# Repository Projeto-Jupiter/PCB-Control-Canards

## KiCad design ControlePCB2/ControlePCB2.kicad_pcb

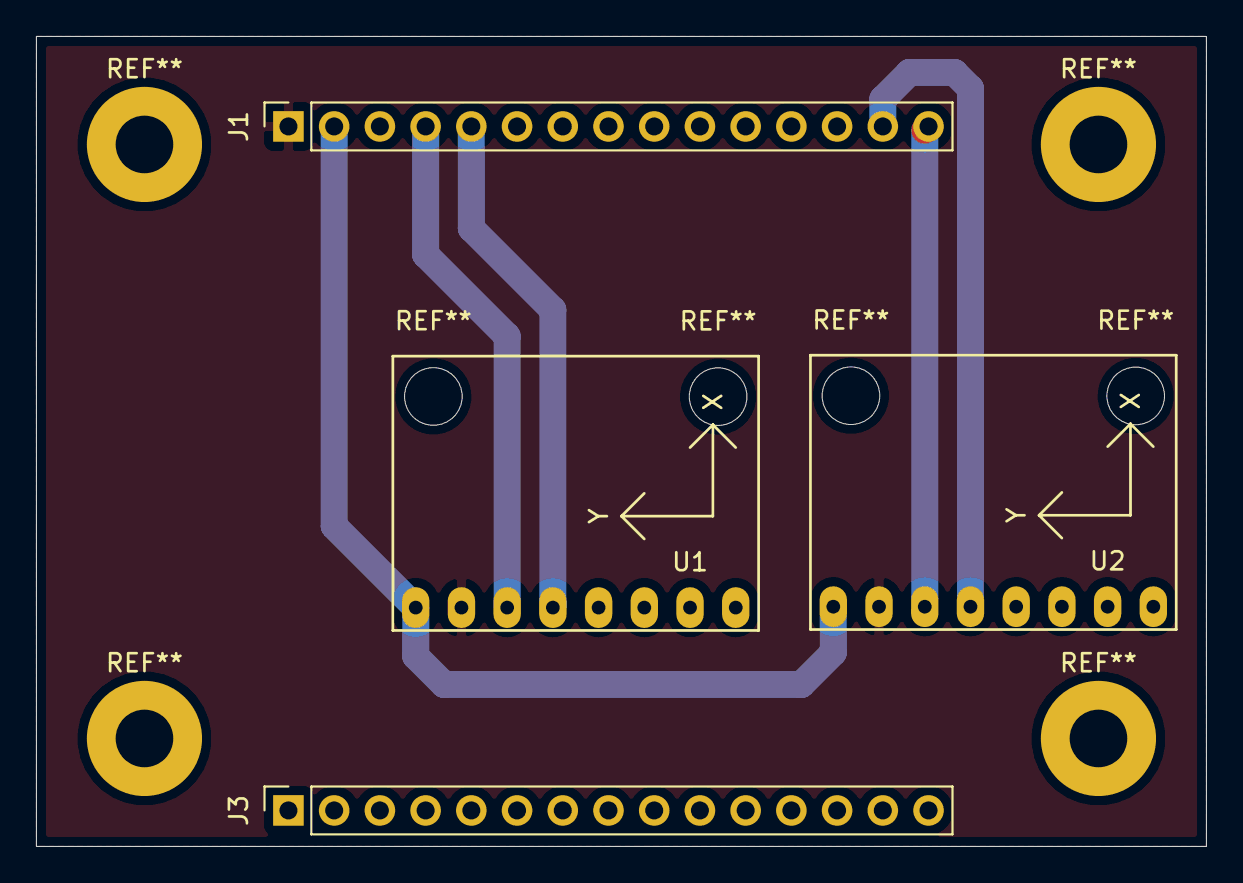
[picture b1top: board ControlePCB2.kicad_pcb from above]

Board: 2 copper layers, 65.0 x 45.0 mm, 4 parts (0 on the bottom side), 6 nets.

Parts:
J1, J3: Conn_01x15_Female; PinSocket_1x15_P2.54mm_Vertical
U1, U2: GY-521-symbols; GY-521

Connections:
+3V3: J1.2, U1.1, U2.1
/SCL0: J1.4, U1.3
/SCL1: J1.15, U2.3
/SDA0: J1.5, U1.4
/SDA1: J1.14, U2.4
GND: J1.1, U1.2, U2.2
